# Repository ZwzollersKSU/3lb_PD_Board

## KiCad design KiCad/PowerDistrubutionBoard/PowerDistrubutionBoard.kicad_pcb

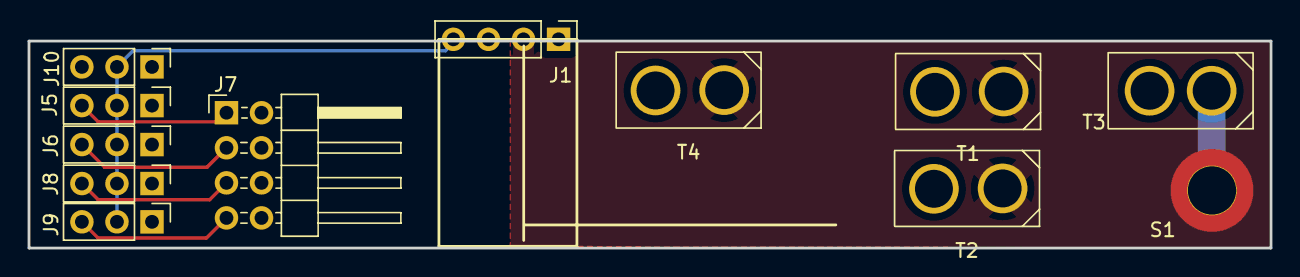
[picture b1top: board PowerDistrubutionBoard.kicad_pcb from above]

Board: 2 copper layers, 90.0 x 15.0 mm, 12 parts (0 on the bottom side), 8 nets.

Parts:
J1: BEC; PinHeader_1x04_P2.54mm_Vertical
J5: Ch1; PinHeader_1x03_P2.54mm_Vertical
J6: Ch2; PinHeader_1x03_P2.54mm_Vertical
J7: S_Out; PinHeader_2x04_P2.54mm_Horizontal
J8: Ch3; PinHeader_1x03_P2.54mm_Vertical
J9: Ch4; PinHeader_1x03_P2.54mm_Vertical
J10: Batt; PinHeader_1x03_P2.54mm_Vertical
S1: Screw_Switch; Screw_Switch_Pad
T1: PWR_D1; XT30
T2: PWR_D2; XT30
T3: PWR_IN; XT30
T4: PWR_W; XT30

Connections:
unnamed: J1.1, T1.1 (+), T2.1 (+), T3.1 (+), T4.1 (+)
unnamed: J1.2, S1.1, S1.2, T1.2 (-), T2.2 (-), T4.2 (-)
unnamed: J1.3, J5.1, J6.1, J7.2, J7.4, J7.6, J7.8, J8.1, J9.1, J10.1
unnamed: J1.4, J5.2, J6.2, J8.2, J9.2, J10.2
unnamed: J5.3, J7.1
unnamed: J6.3, J7.3
unnamed: J7.5, J8.3
unnamed: J7.7, J9.3

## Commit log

2023-09-20 added initial board
2023-10-19 new stuff
2023-10-19 adds maore stuff
